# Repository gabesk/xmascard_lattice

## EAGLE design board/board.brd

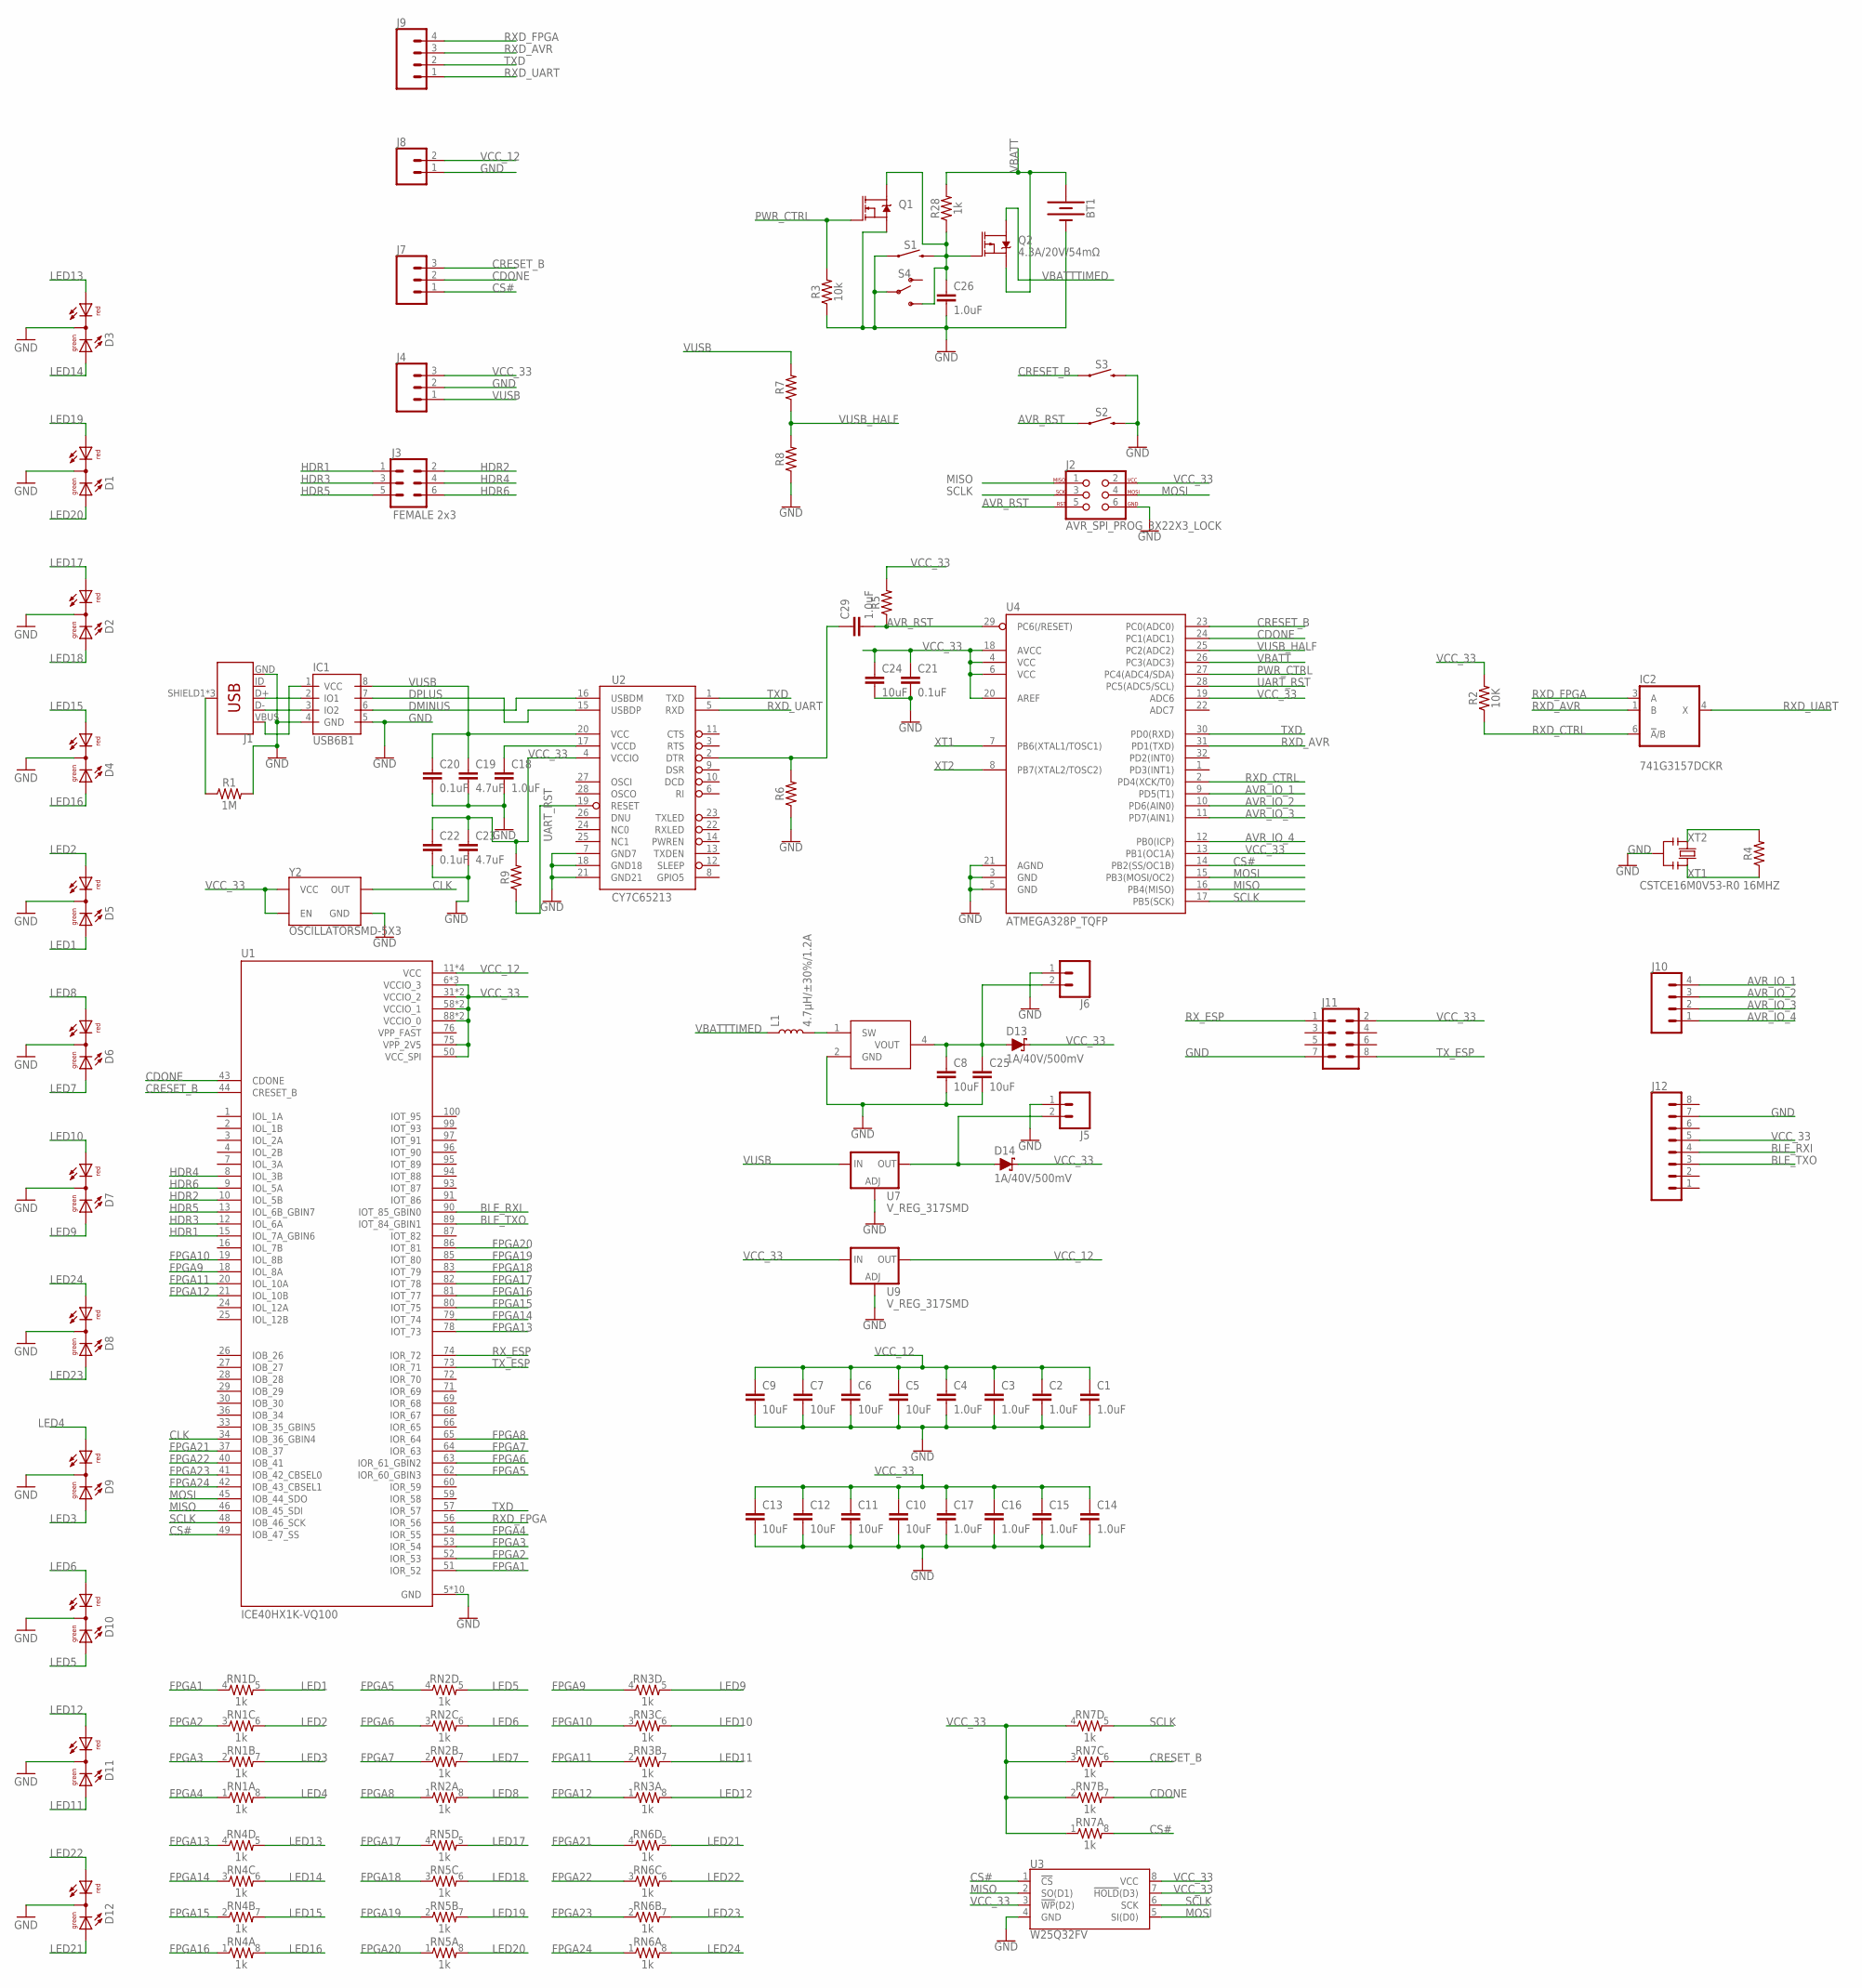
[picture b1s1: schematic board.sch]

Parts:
BT1: BATTERY-20MM_SMD; BATTCON_20MM
C1, C2, C3, C4, C14, C15, C16, C17, C18, C29: 1.0uF; 0805
C5, C6, C7, C8, C9, C10, C11, C12, C13, C24, C25: 10uF; 0805
C19, C23: 4.7uF; 0805
C20, C21, C22: 0.1uF; 0805
C26: 1.0uF; 0603
D1, D2, D3, D4, D5, D6, D7, D8, D9, D10, D11, D12: DUOLED5MM
D13, D14: 1A/40V/500mV; SMA-DIODE
IC1: USB6B1; SO08
IC2: 741G3157DCKR; DCK_R-PDSO-G6
J1: USB_MICRO-B_FEMALE-SMT; USB-B-MICRO-SMD
J2: AVR_SPI_PROG_3X22X3_LOCK; 2X3_LOCK
J3: FEMALE 2x3; 2X3
J4, J7: CONN_03LOCK; 1X03_LOCK
J5, J6, J8: CONN_02LOCK; 1X02_LOCK
J9, J10: CONN_04LOCK; 1X04_LOCK
J11: CONN_04X2; 2X4
J12: CONN_08LOCK; 1X08_LOCK
L1: 4.7µH/±30%/1.2A; INDUCTOR_4.7UH
Q1: 5.8A/30V/35mΩ; SOT23-3
Q2: 4.3A/20V/54mΩ; SOT23-3
R1: 1M; 0805
R2: 10K; 0805
R3: 10k; 0805
R4, R5, R6, R7, R8, R9: 0805
R28: 1k; 0603
RN1, RN2, RN3, RN4, RN5, RN6, RN7: 1k; 0805-ARV
S1, S2, S3: MOMENTARY-SWITCH-SPST-SMD-5.2MM; TACTILE_SWITCH_SMD_5.2MM
S4: SWITCH-SPDT-PTH-11.6X4.0MM; SWITCH_SPDT_PTH_11.6X4.0MM
U1: ICE40HX1K-VQ100; QFP50P1600X1600X120-100N
U2: CY7C65213; SSOP28DB
U3: W25Q32FV; SOIC-8
U4: ATMEGA328P_TQFP; TQFP32-08
U7, U9: V_REG_317SMD; SOT223
U$2: TPS613221A; SOT95P280X145-5N
Y1: CSTCE16M0V53-R0 16MHZ; RESONATOR
Y2: OSCILLATORSMD-5X3; OSCILLATOR-SMD-5X3.2

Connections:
AVR_IO_1: J10.4, U4.9 (PD5(T1))
AVR_IO_2: J10.3, U4.10 (PD6(AIN0))
AVR_IO_3: J10.2, U4.11 (PD7(AIN1))
AVR_IO_4: J10.1, U4.12 (PB0(ICP))
AVR_RST: C29.2, J2.5, R5.1, S2.1, U4.29 (PC6(/RESET))
BLE_RXI: J12.4, U1.90 (IOT_85_GBIN0)
BLE_TXO: J12.3, U1.89 (IOT_84_GBIN1)
CDONE: J7.2, RN7.7 (2), U1.43 (CDONE), U4.24 (PC1(ADC1))
CLK: U1.34 (IOB_36_GBIN4), Y2.3 (OUT)
CRESET_B: J7.3, RN7.6 (2), S3.1, U1.44 (CRESET_B), U4.23 (PC0(ADC0))
CS#: J7.1, RN7.8 (2), U1.49 (IOB_47_SS), U3.1 (!CS!), U4.14 (PB2(SS/OC1B))
DMINUS: IC1.6 (IO2), U2.16 (USBDM)
DPLUS: IC1.7 (IO1), U2.15 (USBDP)
FPGA1: RN1.4 (1), U1.51 (IOR_52)
FPGA2: RN1.3 (1), U1.52 (IOR_53)
FPGA3: RN1.2 (1), U1.53 (IOR_54)
FPGA4: RN1.1, U1.54 (IOR_55)
FPGA5: RN2.4 (1), U1.62 (IOR_60_GBIN3)
FPGA6: RN2.3 (1), U1.63 (IOR_61_GBIN2)
FPGA7: RN2.2 (1), U1.64 (IOR_63)
FPGA8: RN2.1, U1.65 (IOR_64)
FPGA9: RN3.4 (1), U1.18 (IOL_8A)
FPGA10: RN3.3 (1), U1.19 (IOL_8B)
FPGA11: RN3.2 (1), U1.20 (IOL_10A)
FPGA12: RN3.1, U1.21 (IOL_10B)
FPGA13: RN4.4 (1), U1.78 (IOT_73)
FPGA14: RN4.3 (1), U1.79 (IOT_74)
FPGA15: RN4.2 (1), U1.80 (IOT_75)
FPGA16: RN4.1, U1.81 (IOT_77)
FPGA17: RN5.4 (1), U1.82 (IOT_78)
FPGA18: RN5.3 (1), U1.83 (IOT_79)
FPGA19: RN5.2 (1), U1.85 (IOT_80)
FPGA20: RN5.1, U1.86 (IOT_81)
FPGA21: RN6.4 (1), U1.37 (IOB_37)
FPGA22: RN6.3 (1), U1.40 (IOB_41)
FPGA23: RN6.2 (1), U1.41 (IOB_42_CBSEL0)
FPGA24: RN6.1, U1.42 (IOB_43_CBSEL1)
GND: BT1.2 (-), C1.2, C2.2, C3.2, C4.2, C5.2, C6.2, C7.2, C8.2, C9.2, C10.2, C11.2, C12.2, C13.2, C14.2, C15.2, C16.2, C17.2, C18.2, C19.2, C20.2, C21.2, C22.2, C23.2, C24.2, C25.2, C26.2, D1.K (C), D2.K (C), D3.K (C), D4.K (C), D5.K (C), D6.K (C), D7.K (C), D8.K (C), D9.K (C), D10.K (C), D11.K (C), D12.K (C), IC1.4 (GND), IC1.5 (GND), IC2.2 (GND), J1.GND, J2.6, J4.2, J5.1, J6.1, J8.1, J11.7, J12.7, Q1.2 (S), R1.2, R3.1, R6.1, R8.1, S1.1, S2.3 (2), S3.3 (2), S4.2, U1.5 (GND), U1.17 (GND), U1.23 (GND), U1.32 (GND), U1.39 (GND), U1.47 (GND), U1.55 (GND), U1.70 (GND), U1.84 (GND), U1.98 (GND), U2.7 (GND7), U2.18 (GND18), U2.21 (GND21), U3.4 (GND), U4.3 (GND), U4.5 (GND), U4.21 (AGND), U7.1 (ADJ), U9.1 (ADJ), U$2.2 (GND), Y1.2, Y2.2 (GND)
HDR1: J3.1, U1.15 (IOL_7A_GBIN6)
HDR2: J3.2, U1.10 (IOL_5B)
HDR3: J3.3, U1.12 (IOL_6A)
HDR4: J3.4, U1.8 (IOL_3B)
HDR5: J3.5, U1.13 (IOL_6B_GBIN7)
HDR6: J3.6, U1.9 (IOL_5A)
LED1: D5.AG, RN1.5 (2)
LED2: D5.AR, RN1.6 (2)
LED3: D9.AG, RN1.7 (2)
LED4: D9.AR, RN1.8 (2)
LED5: D10.AG, RN2.5 (2)
LED6: D10.AR, RN2.6 (2)
LED7: D6.AG, RN2.7 (2)
LED8: D6.AR, RN2.8 (2)
LED9: D7.AG, RN3.5 (2)
LED10: D7.AR, RN3.6 (2)
LED11: D11.AG, RN3.7 (2)
LED12: D11.AR, RN3.8 (2)
LED13: D3.AR, RN4.5 (2)
LED14: D3.AG, RN4.6 (2)
LED15: D4.AR, RN4.7 (2)
LED16: D4.AG, RN4.8 (2)
LED17: D2.AR, RN5.5 (2)
LED18: D2.AG, RN5.6 (2)
LED19: D1.AR, RN5.7 (2)
LED20: D1.AG, RN5.8 (2)
LED21: D12.AG, RN6.5 (2)
LED22: D12.AR, RN6.6 (2)
LED23: D8.AG, RN6.7 (2)
LED24: D8.AR, RN6.8 (2)
MISO: J2.1, U1.46 (IOB_45_SDI), U3.2 (SO(D1)), U4.16 (PB4(MISO))
MOSI: J2.4, U1.45 (IOB_44_SDO), U3.5 (SI(D0)), U4.15 (PB3(MOSI/OC2))
unnamed: C29.1, R6.2, U2.2 (DTR)
unnamed: C8.1, C25.1, D13.A, J6.2, U$2.4 (VOUT)
unnamed: C18.1, U2.17 (VCCD)
unnamed: J1.SHIELD1 (SHIELD), J1.SHIELD2 (SHIELD), J1.SHIELD3 (SHIELD), R1.1
unnamed: C26.1, Q1.3 (D), Q2.1 (G), R28.1, S1.3 (2), S4.3 (S)
unnamed: D14.A, J5.2, U7.2 (OUT)
unnamed: IC1.2 (IO1), J1.D+
unnamed: IC1.3 (IO2), J1.D-
unnamed: L1.P$2 (2), U$2.1 (SW)
unnamed: IC1.1 (VCC), J1.VBUS
NC1: U2.25 (NC1)
PWR_CTRL: Q1.1 (G), R3.2, U4.27 (PC4(ADC4/SDA))
RXD_AVR: IC2.1 (B), J9.3, U4.31 (PD1(TXD))
RXD_CTRL: IC2.6 (!A!/B), R2.1, U4.2 (PD4(XCK/T0))
RXD_FPGA: IC2.3 (A), J9.4, U1.56 (IOR_56)
RXD_UART: IC2.4 (X), J9.1, U2.5 (RXD)
RX_ESP: J11.1, U1.74 (IOR_72)
SCLK: J2.3, RN7.5 (2), U1.48 (IOB_46_SCK), U3.6 (SCK), U4.17 (PB5(SCK))
TXD: J9.2, U1.57 (IOR_57), U2.1 (TXD), U4.30 (PD0(RXD))
TX_ESP: J11.8, U1.73 (IOR_71)
UART_RST: R9.1, U2.19 (RESET), U4.28 (PC5(ADC5/SCL))
VBATT: BT1.1 (+), Q2.2 (S), R28.2, U4.26 (PC3(ADC3))
VBATTTIMED: L1.P$1 (1), Q2.3 (D)
VCC_12: C1.1, C2.1, C3.1, C4.1, C5.1, C6.1, C7.1, C9.1, J8.2, U1.11 (VCC), U1.35 (VCC), U1.61 (VCC), U1.77 (VCC), U9.2 (OUT)
VCC_33: C10.1, C11.1, C12.1, C13.1, C14.1, C15.1, C16.1, C17.1, C21.1, C22.1, C23.1, C24.1, D13.C, D14.C, IC2.5 (VCC), J2.2, J4.3, J11.2, J12.5, R2.2, R5.2, R9.2, RN7.1, RN7.2 (1), RN7.3 (1), RN7.4 (1), U1.6 (VCCIO_3), U1.14 (VCCIO_3), U1.22 (VCCIO_3), U1.31 (VCCIO_2), U1.38 (VCCIO_2), U1.50 (VCC_SPI), U1.58 (VCCIO_1), U1.67 (VCCIO_1), U1.75 (VPP_2V5), U1.88 (VCCIO_0), U1.92 (VCCIO_0), U2.4 (VCCIO), U3.3 (!WP!(D2)), U3.7 (!HOLD!(D3)), U3.8 (VCC), U4.4 (VCC), U4.6 (VCC), U4.13 (PB1(OC1A)), U4.18 (AVCC), U4.19 (ADC6), U4.20 (AREF), U9.3 (IN), Y2.1 (EN), Y2.4 (VCC)
VPP_FAST: U1.76 (VPP_FAST)
VUSB: C19.1, C20.1, IC1.8 (VCC), J4.1, R7.2, U2.20 (VCC), U7.3 (IN)
VUSB_HALF: R7.1, R8.2, U4.25 (PC2(ADC2))
XT1: R4.1, U4.7 (PB6(XTAL1/TOSC1)), Y1.3
XT2: R4.2, U4.8 (PB7(XTAL2/TOSC2)), Y1.1

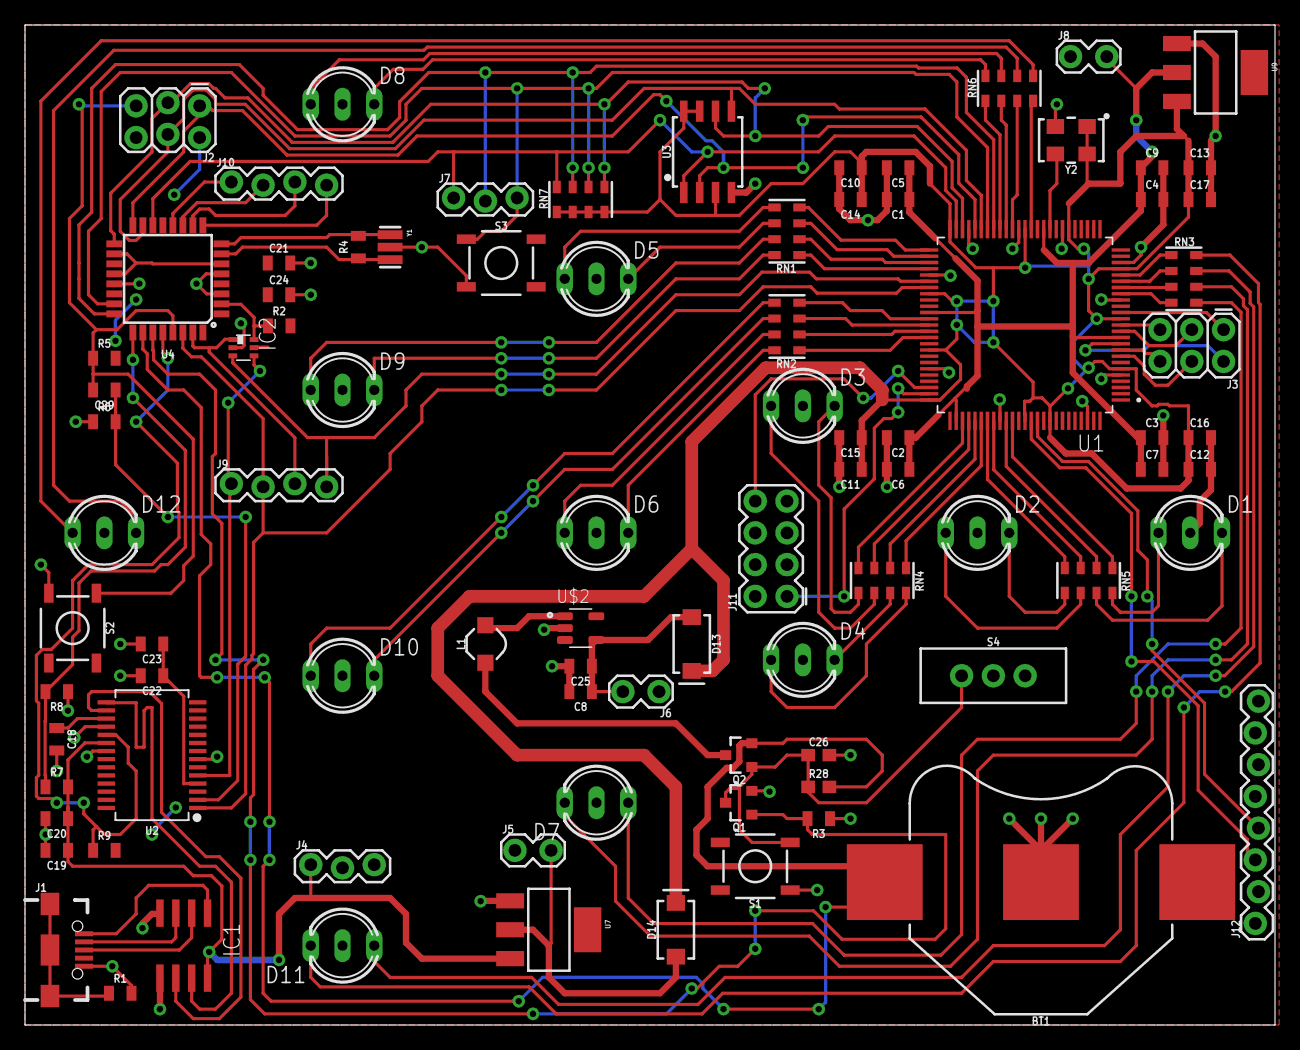
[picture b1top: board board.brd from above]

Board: 2 copper layers, 100.0 x 80.0 mm, 89 parts (0 on the bottom side), 98 nets.

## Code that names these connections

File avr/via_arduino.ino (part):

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

#define PIN_CRESET PINC
#define PIN_CDONE PINC
#define PIN_VBATT PINC
#define PIN_PWR_CTRL PINC
#define PIN_RXD_CTRL PIND


#define BIT_CRESET PINC0
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

void SetupFpgaResetAndDone() {
  // CRESET#  -> pin 23 -> PC0 (ADC0)
  // CDONE_B  -> pin 24 -> PC1 -> input (ADC1)
  // VBATT    -> pin 26 -> PC3 -> analog input (ADC3)
  // PWR_CTRL -> pin 27 -> PC4 -> output (ADC4)
  // RXD_CTRL -> pin 2  -> PD4 -> output
  //
  // Normally CRESET is open-circuit so it can float high
  // When we want to reset the FPGA, turn it to an input, low, so it pulls the FPGA low
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}

unsigned char ReadFpgaDoneBit() {
  if (PIN_CDONE & (1 << BIT_CDONE)) return 1;
  else return 0;
}

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
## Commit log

2019-07-24 Further updates
2019-12-01 Also call the programming Python file; fix the toolchain location if they are not on C:
2019-12-01 Add example blank and blink HDL files.

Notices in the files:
parts and their libraries:
SparkFun-IC-Memory: Licensing: Creative Commons ShareAlike 4.0 International - https://creativecommons.org/licenses/by-sa/4.0
